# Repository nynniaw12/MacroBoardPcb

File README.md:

# MacroBoardPcb

PCB for a custom Macroboard.

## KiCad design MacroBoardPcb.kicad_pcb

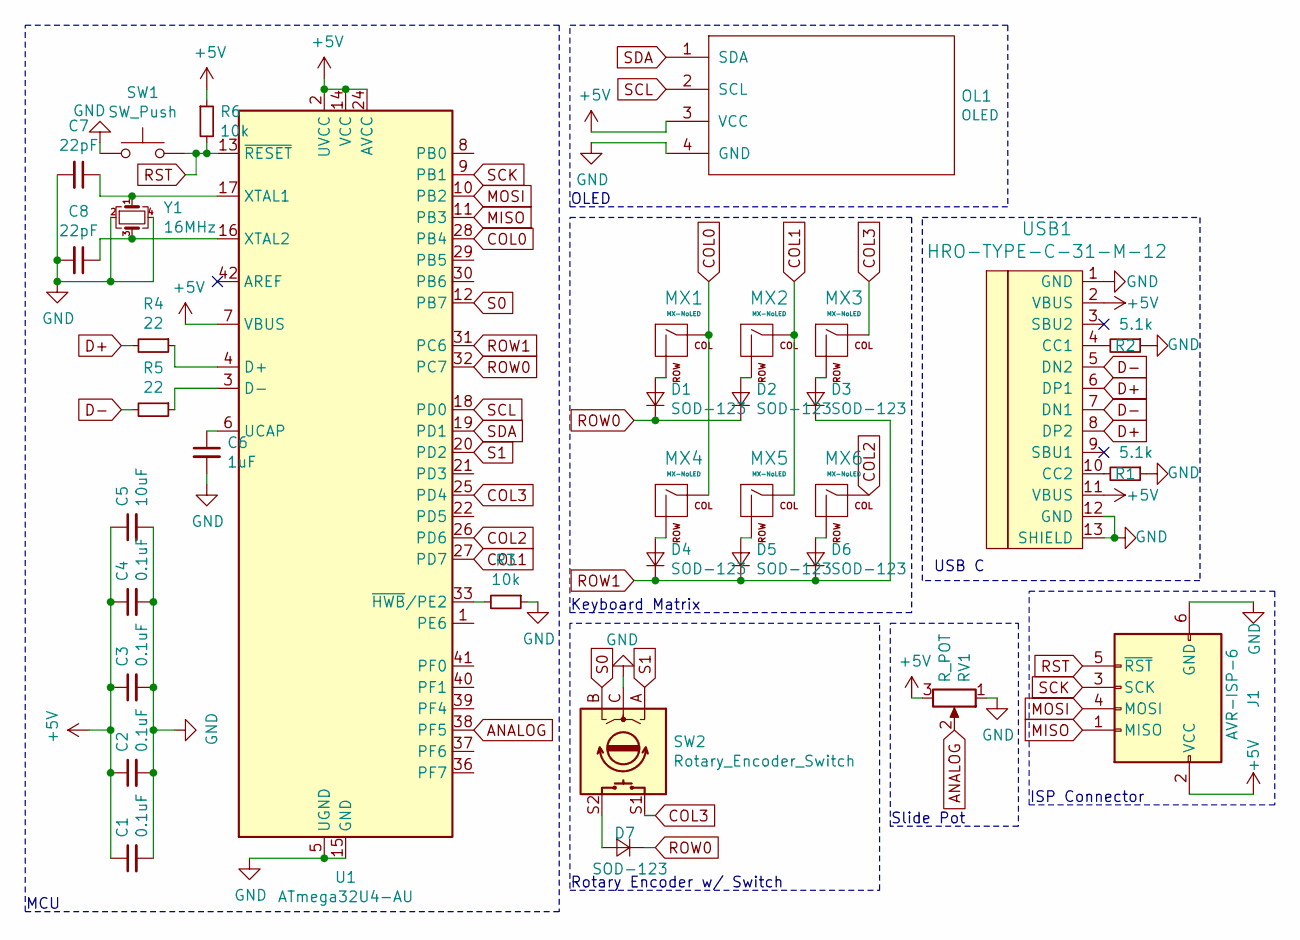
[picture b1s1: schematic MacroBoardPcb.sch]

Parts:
C1, C2, C3, C4: 0.1uF; C_0805_2012Metric
C5: 10uF; C_0805_2012Metric
C6: 1uF; C_0805_2012Metric
C7, C8: 22pF; C_0805_2012Metric
D1, D2, D3, D4, D5, D6, D7: SOD-123; D_SOD-123
J1: AVR-ISP-6; PinHeader_2x03_P2.54mm_Vertical
MX1, MX2, MX3, MX4, MX5, MX6: MX-NoLED; MX-1U-NoLED
OL1: OLED; OLED_v2
R1, R2: 5.1k; R_0805_2012Metric
R3, R6: 10k; R_0805_2012Metric
R4, R5: 22; R_0805_2012Metric
RV1: R_POT; Potentiometer_Bourns_PTA6043_Single_Slide
SW1: SW_Push; SKQG-1155865
SW2: Rotary_Encoder_Switch; RotaryEncoder_Alps_EC11E-Switch_Vertical_H20mm
U1: ATmega32U4-AU; TQFP-44_10x10mm_P0.8mm
USB1: HRO-TYPE-C-31-M-12
Y1: 16MHz; Crystal_SMD_3225-4Pin_3.2x2.5mm

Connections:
+5V: C1.1, C2.1, C3.1, C4.1, C5.1, J1.2 (VCC), OL1.3 (VCC), R6.1, RV1.3, U1.2 (UVCC), U1.7 (VBUS), U1.14 (VCC), U1.24 (AVCC), U1.34 (VCC), U1.44 (AVCC), USB1.2 (VBUS), USB1.11 (VBUS)
ANALOG: RV1.2, U1.38 (PF5)
COL0: MX1.1 (COL), MX4.1 (COL), U1.28 (PB4)
COL1: MX2.1 (COL), MX5.1 (COL), U1.27 (PD7)
COL2: MX6.1 (COL), U1.26 (PD6)
COL3: MX3.1 (COL), SW2.S1, U1.25 (PD4)
D+: R4.2, USB1.6 (DP1), USB1.8 (DP2)
D-: R5.2, USB1.5 (DN2), USB1.7 (DN1)
GND: C1.2, C2.2, C3.2, C4.2, C5.2, C6.2, C7.2, C8.2, J1.6 (GND), OL1.4 (GND), R1.1, R2.1, R3.1, RV1.1, SW1.1, SW2.C, U1.5 (UGND), U1.15 (GND), U1.23 (GND), U1.35 (GND), U1.43 (GND), USB1.1 (GND), USB1.12 (GND), USB1.13 (SHIELD), Y1.2, Y1.4
MISO: J1.1 (MISO), U1.11 (PB3)
MOSI: J1.4 (MOSI), U1.10 (PB2)
unnamed: C6.1, U1.6 (UCAP)
unnamed: C7.1, U1.17 (XTAL1), Y1.1
unnamed: C8.1, U1.16 (XTAL2), Y1.3
unnamed: D1.2 (A), MX1.2 (ROW)
unnamed: D2.2 (A), MX2.2 (ROW)
unnamed: D3.2 (A), MX3.2 (ROW)
unnamed: D4.2 (A), MX4.2 (ROW)
unnamed: D5.2 (A), MX5.2 (ROW)
unnamed: D6.2 (A), MX6.2 (ROW)
unnamed: D7.2 (A), SW2.S2
unnamed: R1.2, USB1.10 (CC2)
unnamed: R2.2, USB1.4 (CC1)
unnamed: R3.2, U1.33 (~HWB~/PE2)
unnamed: R4.1, U1.4 (D+)
unnamed: R5.1, U1.3 (D-)
ROW0: D1.1 (K), D2.1 (K), D7.1 (K), U1.32 (PC7)
ROW1: D3.1 (K), D4.1 (K), D5.1 (K), D6.1 (K), U1.31 (PC6)
RST: J1.5 (~RST), R6.2, SW1.2, U1.13 (~RESET)
S0: SW2.B, U1.12 (PB7)
S1: SW2.A, U1.20 (PD2)
SCK: J1.3 (SCK), U1.9 (PB1)
SCL: OL1.2 (SCL), U1.18 (PD0)
SDA: OL1.1 (SDA), U1.19 (PD1)

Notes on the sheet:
OLED
Keyboard Matrix
Rotary Encoder w/ Switch
MCU
USB C
Slide Pot
ISP Connector

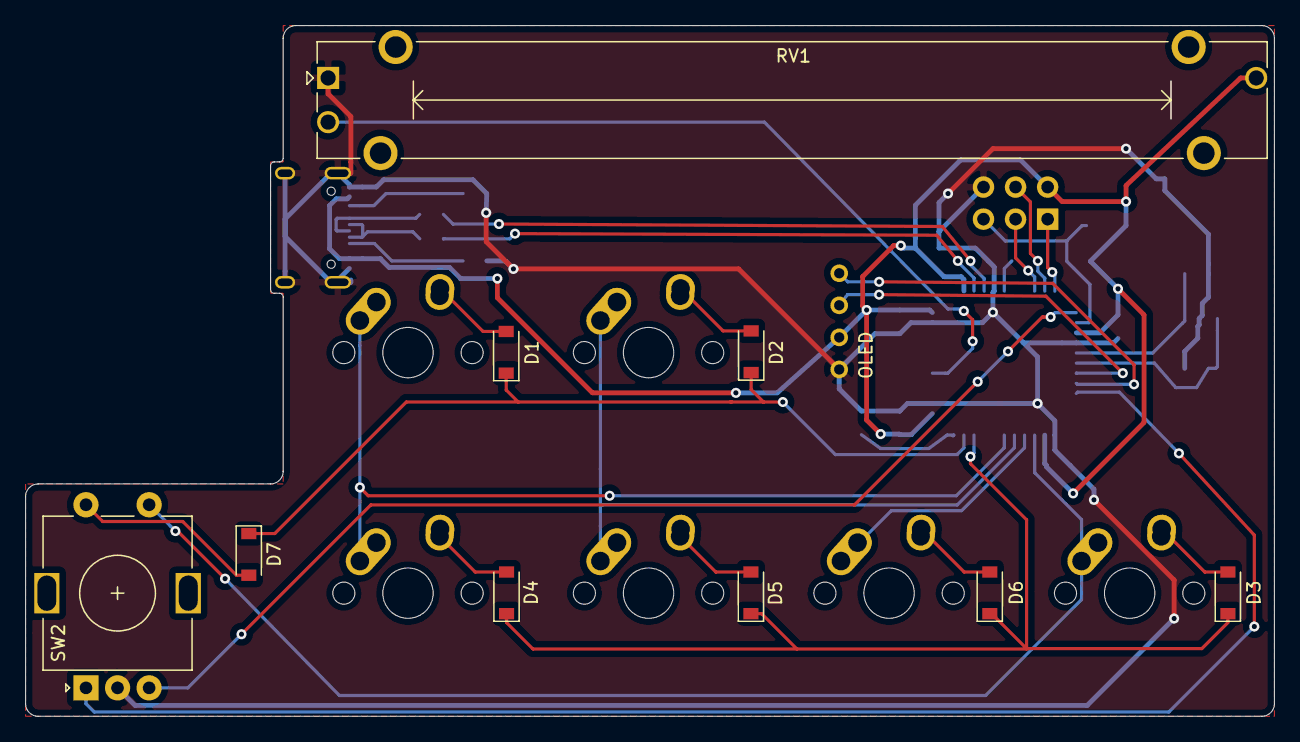
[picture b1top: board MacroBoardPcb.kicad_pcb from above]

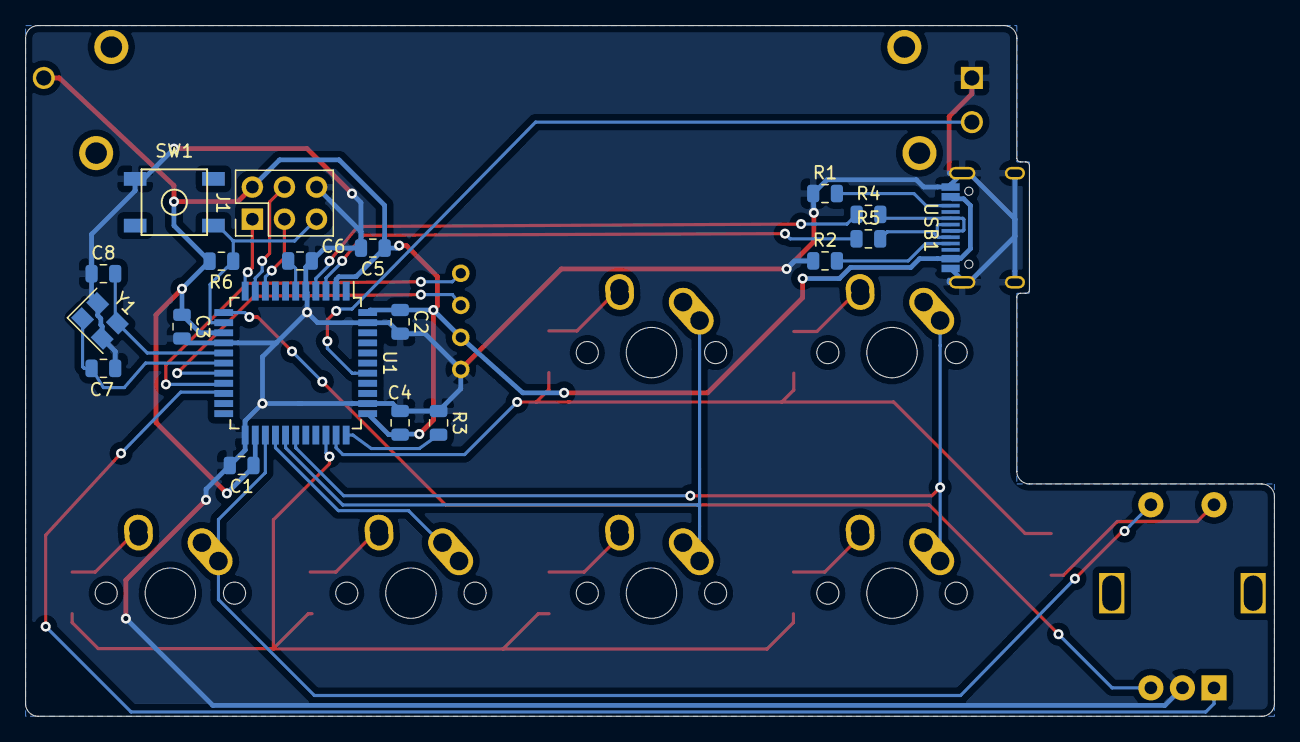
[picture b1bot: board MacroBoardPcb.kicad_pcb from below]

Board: 2 copper layers, 98.9 x 54.7 mm, 35 parts (19 on the bottom side), 34 nets.

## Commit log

2020-09-13 Created KiCad Project
2020-09-13 added submodules
2020-09-13 added oled repo
2020-09-13 finished readying symbols and footprints
2020-09-13 finished schematics
2020-09-14 added footprints and fully finished schematics
2020-09-15 finished routing
2020-09-16 finished with small modifications
2020-09-17 added ground fills
